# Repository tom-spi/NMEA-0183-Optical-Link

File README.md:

# NMEA-0183-Optical-Link
FdEng Marine Electrical &amp; Electronic: Final Project. NMEA 0183 multiplexed fiber optic link. 
# Abstract
The standardised protocol between navigation & communication equipment on board merchant vessels is NMEA 0183. The NMEA 0183 protocol utilises the TIA/EIA 422-B serial data standard as its transmission medium [1]. The TIA/EIA 422-B standard (Commonly referred to as RS422), is a balanced double-current interchange circuit that supports data rates of up to 10Mbit/s [2]. The electrical configuration of RS422 employs a matched twisted pair that can support wire lengths of up to 4Km. In practice, shielded data cable (CAT5 STP & above) is commonly employed which offers good noise immunity to some extent. The effective noise immunity and long transmission distances can only be achieved given correct termination and separation from EMI & noise sources. 

On board a vessel, there may be a need to run long lengths of NMEA (or any RS422/485 type protocol) through areas of high EMI or electrical noise. For example, a transducer mounted on the aft of the vessel may have to run its NMEA cable(s) via the engine room to reach the bridge, this may pass through switchboard rooms, converter rooms and may also be run alongside or very close to high voltage conductors. All these areas can pose challenges due to the high levels of electrical noise and EMI. 

Utilising an optical based link means the transmission medium for the NMEA data is completely immune to any sources of noise, meaning the optical cable can be run alongside any other conductor. This can reduce costs by eliminating the need for extra deck/bulkhead penetrations, fire rated glands and additional time needed to implement the segregation of power and data conductors. Along with this, the fibre can be used as a “backbone”, carrying multiple NMEA sentences down a single fibre, eliminating the need to run multiple fibres or multiple STP cables. This can be particularly useful in a situation where there is a cluster of NMEA devices located a considerable distance from the bridge (i.e. up forward or up mast). Additionally, there is no possibility of ground loops across the optical link and the NMEA devices at each end of the optical link can be considered to be optically isolated from one another.

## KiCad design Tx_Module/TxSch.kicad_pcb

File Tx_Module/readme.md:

This folder contains the KiCAD files, PCB Gerber files and software written for the Tx Module.

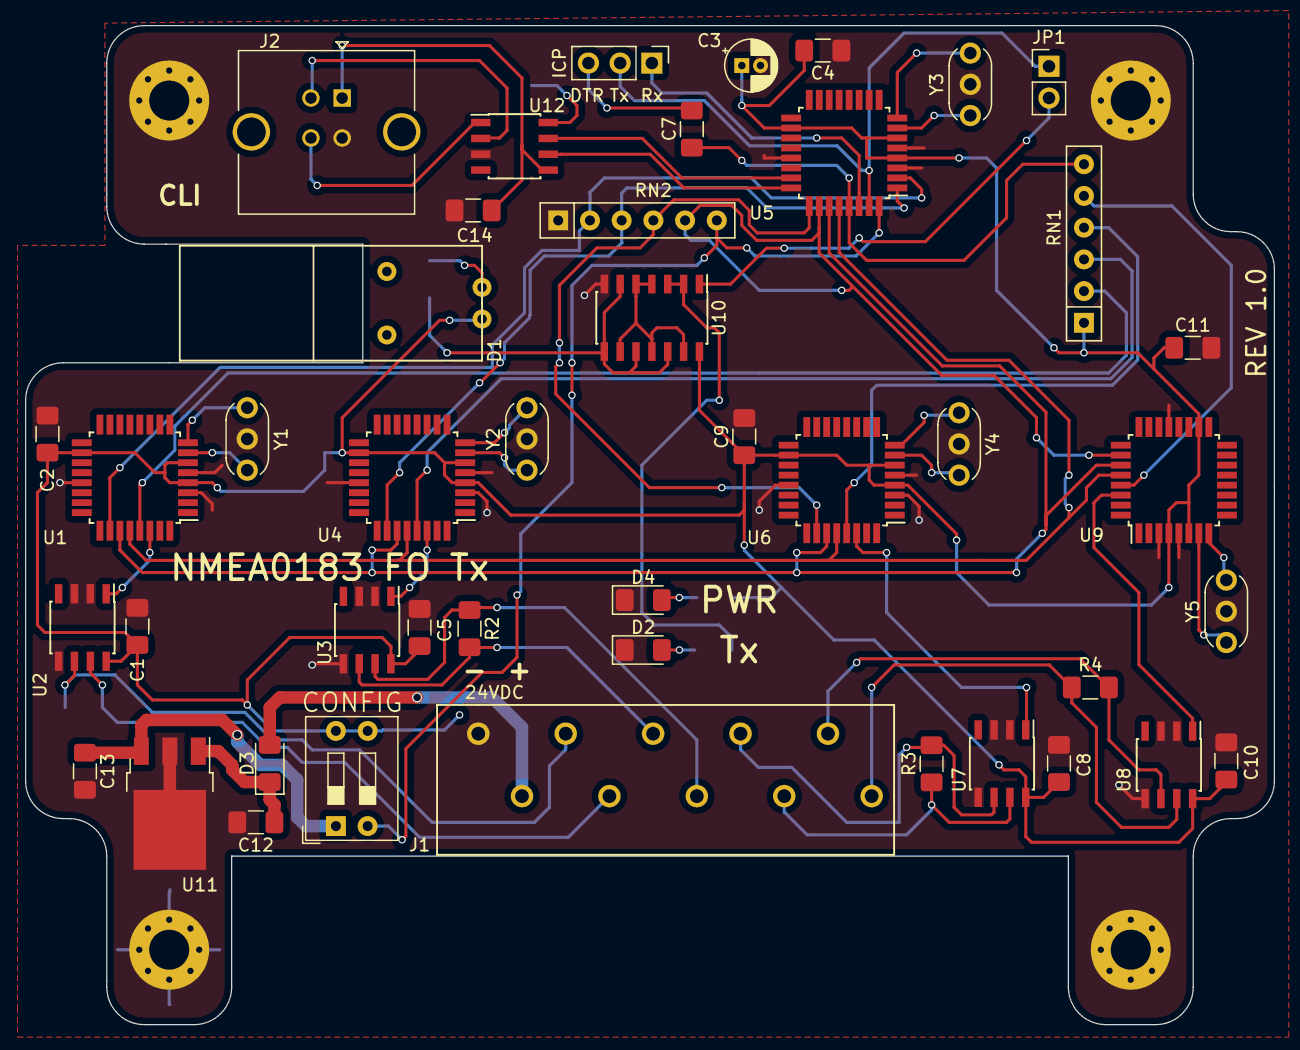
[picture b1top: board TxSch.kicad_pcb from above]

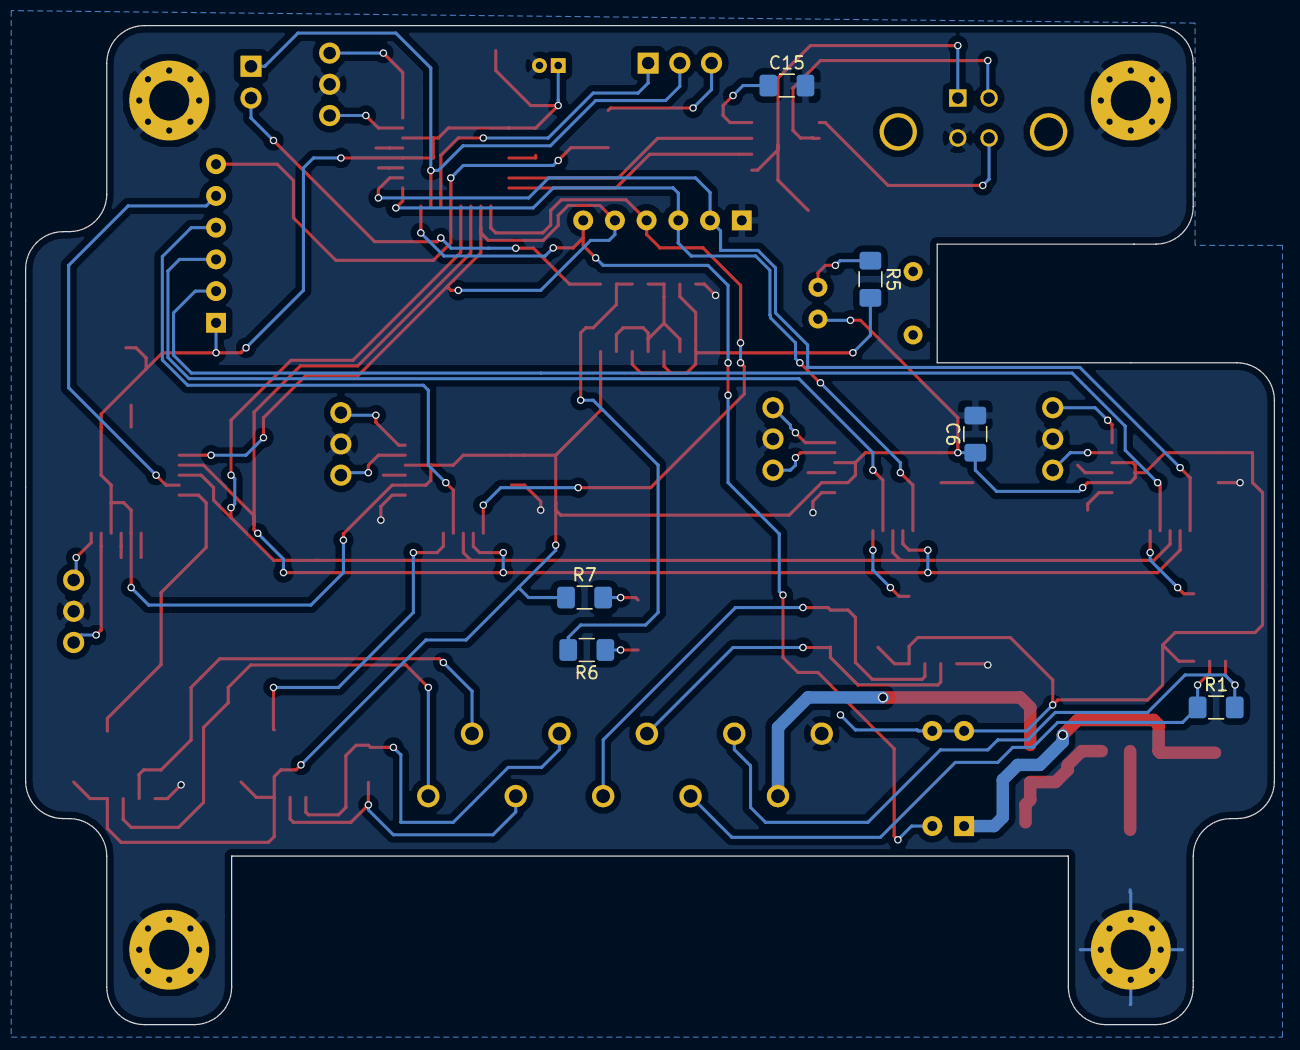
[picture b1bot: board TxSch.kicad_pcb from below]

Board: 2 copper layers, 100.0 x 80.0 mm, 50 parts (6 on the bottom side), 55 nets.

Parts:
C1, C2, C4, C5, C6, C7, C8, C9, C10, C11, C13, C14, C15: 0.1uF; C_1206_3216Metric_Pad1.42x1.75mm_HandSolder
C3: 4.7uF; CP_Radial_D4.0mm_P1.50mm
C12: 0.22uF; C_1206_3216Metric_Pad1.42x1.75mm_HandSolder
CONFIG: SW_DIP_x02; SW_DIP_SPSTx02_Slide_9.78x7.26mm_W7.62mm_P2.54mm
D1: SFH756V
D2: Tx; LED_1206_3216Metric_Pad1.42x1.75mm_HandSolder
D3: 1N4001W; D_1206_3216Metric_Pad1.42x1.75mm_HandSolder
D4: PWR; LED_1206_3216Metric_Pad1.42x1.75mm_HandSolder
ICP: ICP; PinHeader_1x03_P2.54mm_Vertical
J1: PwR & NMEA In; 10PPush_in_Conn
J2: CLI_USB; USB_B_TE_5787834_Vertical
JP1: ICP; PinHeader_1x02_P2.54mm_Vertical
R1, R2, R3, R4: 120R; R_1206_3216Metric_Pad1.42x1.75mm_HandSolder
R5, R6, R7: 330R; R_1206_3216Metric_Pad1.42x1.75mm_HandSolder
RN1, RN2: 10K; R_Array_SIP6
U1, U4, U5, U6, U9: ATmega328P-AU; TQFP-32_7x7mm_P0.8mm
U2, U3, U7, U8: MAX485E; SOIC-8_3.9x4.9mm_P1.27mm
U10: 74HC14; SOIC-14_3.9x8.7mm_P1.27mm
U11: L7805; TO-252-3_TabPin2
U12: CH330N; SOIC-8_3.9x4.9mm_P1.27mm
Y1, Y2, Y3, Y4, Y5: 16MHz; Resonator-3Pin_W6.0mm_H3.0mm

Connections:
+5V: C1.1, C2.1, C3.1, C4.1, C5.1, C6.1, C8.1, C9.1, C10.1, C11.1, CONFIG.3, CONFIG.4, D1.2, R7.1, RN1.1, U1.4, U1.6, U1.18, U2.8, U3.8, U4.4, U4.6, U4.18, U5.4, U5.6, U5.18, U6.4, U6.6, U6.18, U7.8, U8.8, U9.4, U9.6, U9.18, U10.14
/A_RTS: RN2.2, U1.26, U5.2
/B_RTS: RN2.3, U4.26, U5.1
/CLI_EN: CONFIG.2, RN2.6, U5.32
/C_RTS: RN2.4, U5.25, U6.26
/D_RTS: RN2.5, U5.26, U9.26
/FO_Tx: JP1.2, U10.1
/PwR_Sw: C13.1, CONFIG.1, U11.3
/R1: RN1.2, U1.29
/R2: RN1.3, U4.29
/R3: RN1.4, U6.29
/R4: RN1.5, U9.29
/R_MUX: C7.1, RN1.6, U5.29
/RxA_+: J1.3, R1.2, U2.6
/RxA_-: J1.4, R1.1, U2.7
/RxB_+: J1.5, R2.2, U3.6
/RxB_-: J1.6, R2.1, U3.7
/RxC_+: J1.7, R3.2, U7.6
/RxC_-: J1.8, R3.1, U7.7
/RxD_+: J1.9, R4.2, U8.6
/RxD_-: J1.10, R4.1, U8.7
/Rx_A_TTL: U1.30, U2.1
/Rx_B_TTL: U3.1, U4.30
/Rx_C_TTL: U6.30, U7.1
/Rx_D_TTL: U8.1, U9.30
/SCL: U1.28, U4.28, U5.28, U6.28, U9.28
/SDA: U1.27, U4.27, U5.27, U6.27, U9.27
/UART_DTR: C7.2, ICP.3
/UART_Rx: ICP.1, U5.30
/UART_Tx: ICP.2, JP1.1, U5.31
/USB_Rx: U5.23, U12.7
/USB_Tx: U5.24, U12.6
GND: C1.2, C2.2, C3.2, C4.2, C5.2, C6.2, C8.2, C9.2, C10.2, C11.2, C12.2, C13.2, C14.2, C15.2, D2.1, D4.1, J1.1, J2.4, RN2.1, U1.3, U1.5, U1.21, U2.2, U2.3, U2.5, U3.2, U3.3, U3.5, U4.3, U4.5, U4.21, U5.3, U5.5, U5.21, U6.3, U6.5, U6.21, U7.2, U7.3, U7.5, U8.2, U8.3, U8.5, U9.3, U9.5, U9.21, U10.7, U11.2, U12.3, Y1.2, Y2.2, Y3.2, Y4.2, Y5.2
unnamed: C12.1, D3.1, U11.1
unnamed: C14.1, J2.1, U12.5
unnamed: C15.1, U12.8
unnamed: D1.1, R5.1
unnamed: D2.2, R6.1
unnamed: D3.2, J1.2
unnamed: D4.2, R7.2
unnamed: J2.2, U12.2
unnamed: J2.3, U12.1
unnamed: R5.2, U10.6, U10.8, U10.10, U10.12
unnamed: R6.2, U10.2, U10.3
unnamed: U1.7, Y1.3
unnamed: U1.8, Y1.1
unnamed: U4.7, Y2.1
unnamed: U4.8, Y2.3
unnamed: U5.7, Y3.1
unnamed: U5.8, Y3.3
unnamed: U6.7, Y4.3
unnamed: U6.8, Y4.1
unnamed: U9.7, Y5.1
unnamed: U9.8, Y5.3
unnamed: U10.4, U10.5, U10.9, U10.11, U10.13

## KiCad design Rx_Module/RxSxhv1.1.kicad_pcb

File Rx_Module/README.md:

This folder contains the KiCAD files, PCB Gerber files and software written for the Rx Module.

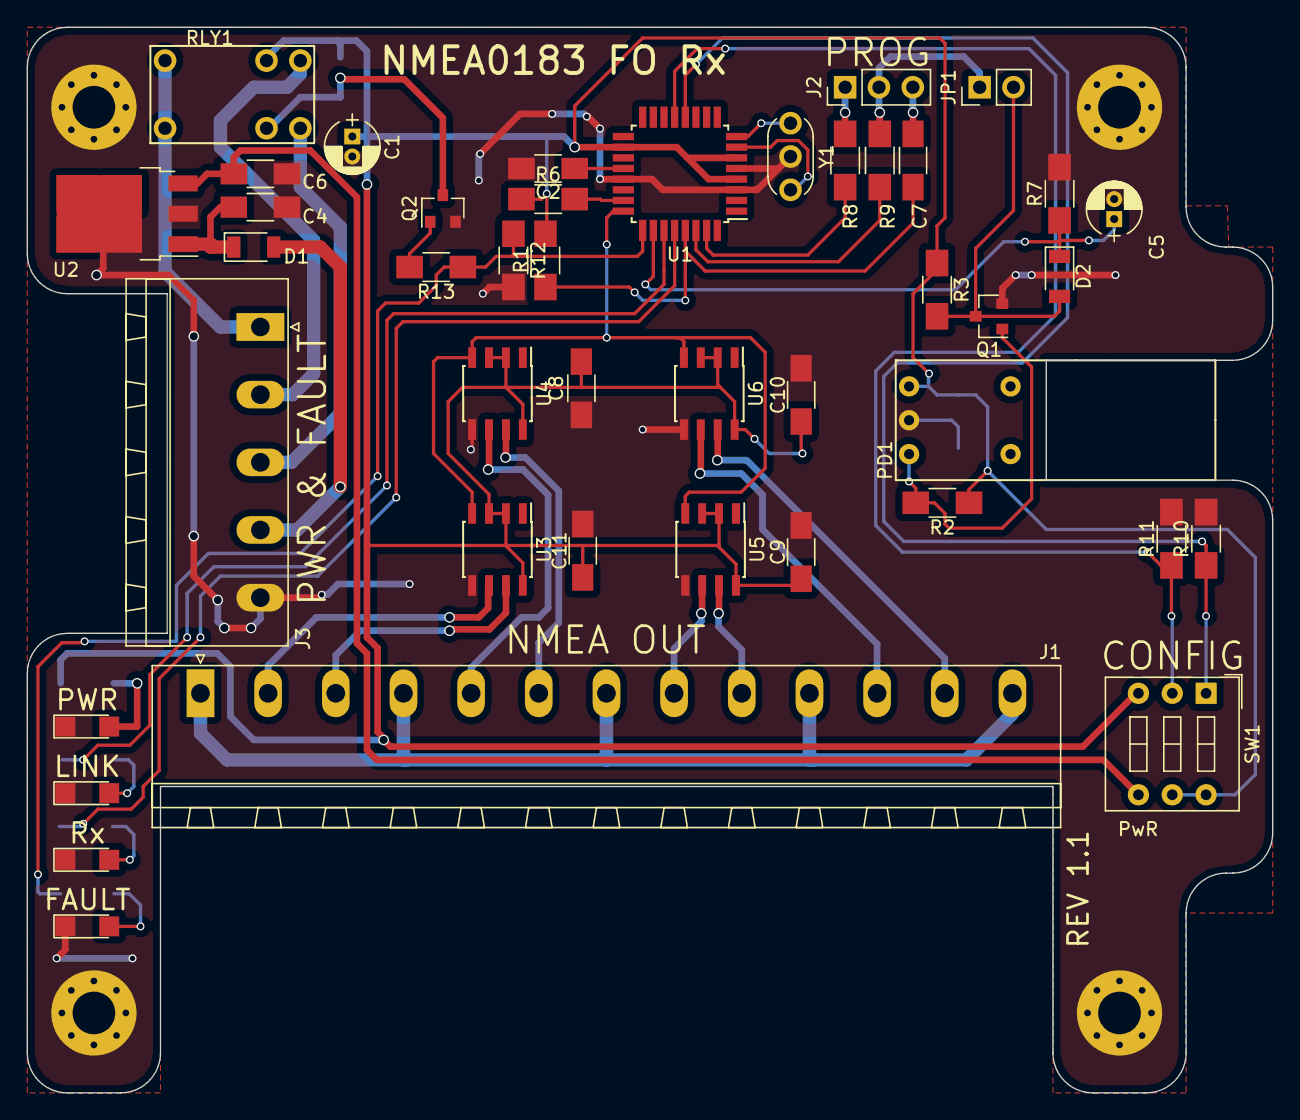
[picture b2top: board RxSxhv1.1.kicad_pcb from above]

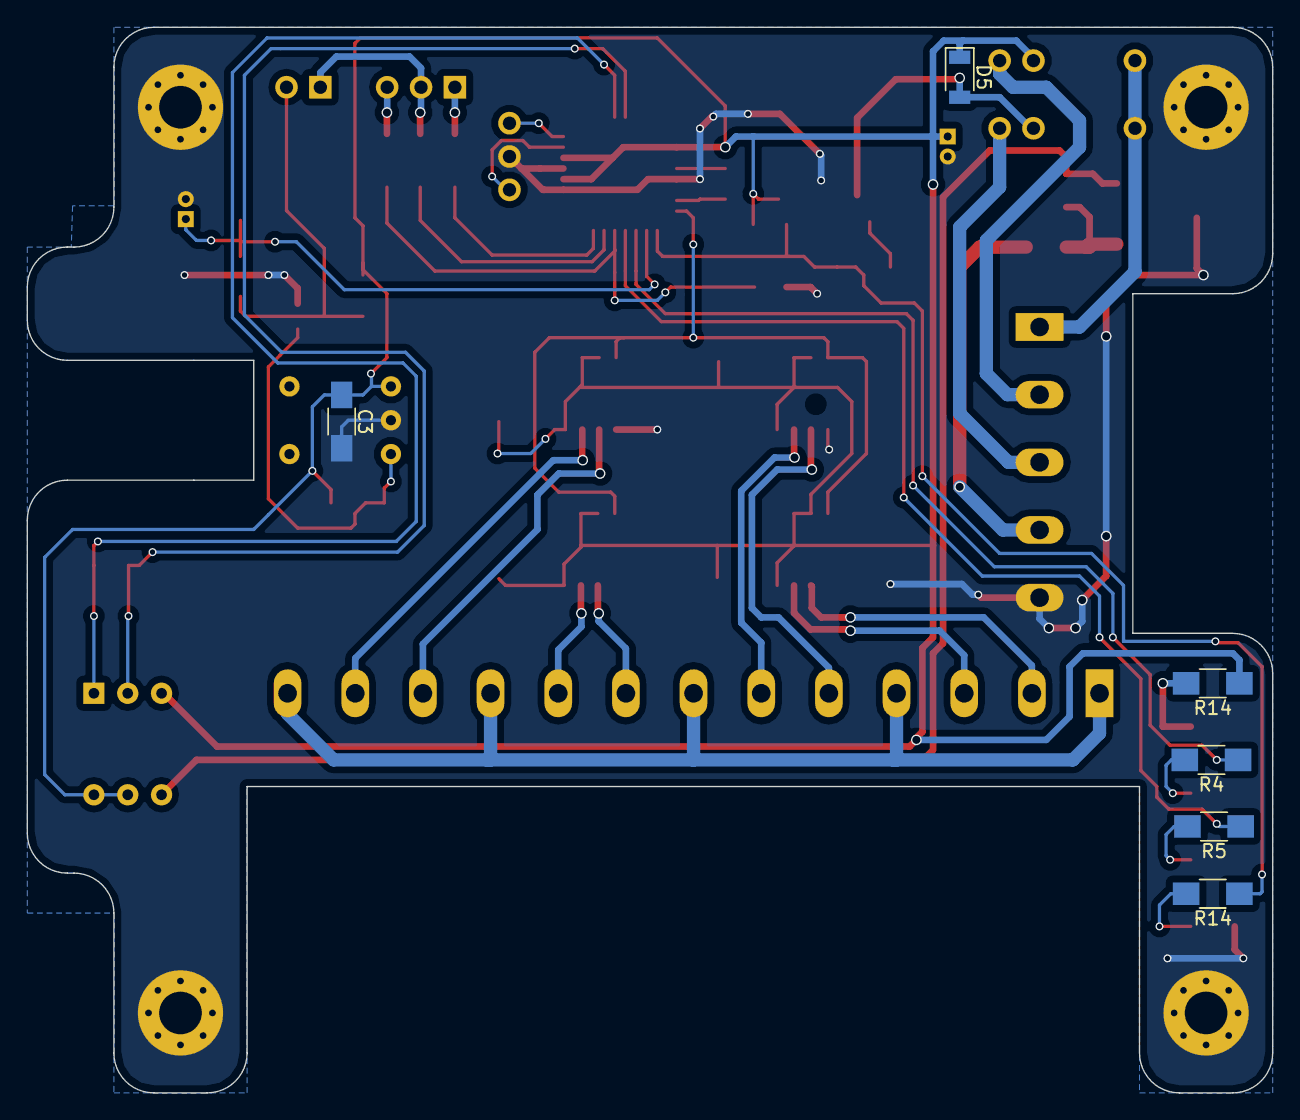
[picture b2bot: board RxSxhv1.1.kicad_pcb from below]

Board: 2 copper layers, 93.5 x 80.0 mm, 49 parts (6 on the bottom side), 41 nets.

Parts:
C1: 4.7u; CP_Radial_D4.0mm_P1.50mm
C2, C7: 100n; C_1206_HandSoldering
C3: 100nF; C_1206_HandSoldering
C4: 0.22u; C_1206_HandSoldering
C5: 4.7uF; CP_Radial_D4.0mm_P1.50mm
C6, C8, C9, C10, C11: 0.1u; C_1206_HandSoldering
D1, D2, D5: 1N4001W; D_1206
FAULT: LED_1206
J1: NMEA; PhoenixContact_MSTBA-G_13x5.08mm_Angled
J2: Prog; Pin_Header_Straight_1x03_Pitch2.54mm
J3: PwR & Fault; PhoenixContact_MSTBA-G_05x5.08mm_Angled
JP1: Jumper_NC_Small; Pin_Header_Straight_1x02_Pitch2.54mm
LINK: Link; LED_1206
PD1: SFH551
PWR: PwR; LED_1206
Q1, Q2: 2N3904; SOT-23
R1, R2, R3, R6, R10, R11: 10K; R_1206_HandSoldering
R4, R5, R14, R14#2: 330R; R_1206_HandSoldering
R7: 100K; R_1206_HandSoldering
R8, R9: 1K; R_1206_HandSoldering
R12: 10k; R_1206_HandSoldering
R13: 1k; R_1206_HandSoldering
RLY1: G5V-1
Rx: Rx; LED_1206
SW1: Config; SW_DIP_x3_W7.62mm_Slide
U1: ATMEGA328P-AU; TQFP-32_7x7mm_Pitch0.8mm
U2: L7805; TO-252-3_TabPin4
U3, U4, U5, U6: MAX485E; SOIC-8_3.9x4.9mm_Pitch1.27mm
Y1: 16MHz; Resonator-3pin_w6.0mm_h3.0mm

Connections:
+5V: C1.1, C3.1, C8.1, C9.1, C10.1, C11.1, D5.1, PD1.3, R1.2, R2.1, R3.1, R6.1, R14#2.1, RLY1.4, SW1.3, SW1.5, SW1.6, U1.4, U1.6, U1.18, U3.2, U3.3, U3.8, U4.2, U4.3, U4.8, U5.2, U5.3, U5.8, U6.2, U6.3, U6.8
/+5V_Sw: C6.1, SW1.4, U2.3
/COM: J3.1, RLY1.5, RLY1.6
/Config_0: R10.1, SW1.1, U1.12
/Config_1: R11.1, SW1.2, U1.13
/Fibre_Rx_TTL: D2.2, JP1.2, Q1.3, R3.2
/Link: C5.1, D2.1, R7.1, U1.26
/Link_Fail: R12.1, R13.1, R14.1, U1.25
/Link_Fail_NC: J3.3, RLY1.2
/Link_Fail_NO: J3.2, RLY1.1
/Link_LED: R4.1, U1.27
/PwR: D1.2, J3.4
/RS422TTL: U1.24, U3.4, U4.4, U5.4, U6.4
/RX_LED: R5.1, U1.28
/Reset: C7.1, R1.1, U1.29
/TxA+: J1.2, U3.6
/TxA-: J1.3, U3.7
/TxB+: J1.5, U4.6
/TxB-: J1.6, U4.7
/TxC+: J1.8, U5.6
/TxC-: J1.9, U5.7
/TxD+: J1.11, U6.6
/TxD-: J1.12, U6.7
Earth: J1.1, J1.4, J1.7, J1.10, J1.13
GND: C1.2, C2.2, C3.2, C4.2, C5.2, C6.2, C8.2, C9.2, C10.2, C11.2, FAULT.1, J3.5, LINK.1, PD1.2, PWR.1, Q1.2, Q2.2, R7.2, R10.2, R11.2, R12.2, Rx.1, U1.3, U1.5, U1.21, U2.2, U2.4, U3.5, U4.5, U5.5, U6.5, Y1.2
unnamed: C2.1, U1.20
unnamed: C4.1, D1.1, U2.1
unnamed: C7.2, J2.3
unnamed: LINK.2, R4.2
unnamed: R5.2, Rx.2
unnamed: D5.2, Q2.3, RLY1.3
unnamed: PWR.2, R14#2.2
unnamed: J2.1, R9.1
unnamed: J2.2, JP1.1, R8.2
unnamed: PD1.1, Q1.1, R2.2
unnamed: Q2.1, R13.2
unnamed: R6.2, U1.23
unnamed: R8.1, U1.30
unnamed: R9.2, U1.31
unnamed: U1.7, Y1.3
unnamed: U1.8, Y1.1

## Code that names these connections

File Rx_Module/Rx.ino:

/*
|--------------------------------------------------------------------------------------------|
|                        --NMEA 0183 OPTICAL LINK Rx MODULE--                                |
|                                                                                            |
|                                                                                            |
|  Project        NMEA_FO.proj                                                               |
|  Program Name 	Rx_v1.1.ino                                                                |
|  Author		     	Thomas Spires 															                               |
|															                                                               |
|  Author Info:                                                                              |
|  Firmware to be written to U1 (ATMEGA328P) on Rx PCB: refer to KiCAD .kicad_pcb            |
|  "RxPCBV1.1"                                                                               |
|                                                                                            |
|  Revision Release Info:                                                                    |
|  20181210 00:42    Tspires      1.0      Initial Deployment on prototype PCB               |
|  20181219 03:13    Tspires      1.1      Added baud rate config + link status              |
|										   function.                                                             |
|--------------------------------------------------------------------------------------------|
*/

#include <SoftwareSerial.h>					//include Bit-Banged serial port hex files

SoftwareSerial RS422Serial(A0, A1); 		// RX, TX // Set BitBanged serial port registers accordingly

// Declare Global Variables

char rx_byte;								//Initialise ASCII Char byte to be passed from Hardware UART buffer

// Declare Pin Names

#define RX_LED A5
#define Link_LED A4
#define Link_Stat A3
#define Link_Fail A2
#define Config_Bit0 8
#define Config_Bit1 9

//Initialise Registers & Interfaces

void setup() {
  //Initialise UARTs
  Serial.begin(19200);						//Start hardware UART & set registers for 19200 Baud
  //Set GPIO Registers
  pinMode(Config_Bit0, INPUT);
  pinMode(Config_Bit1, INPUT);
  pinMode(Link_Stat, INPUT);
  pinMode(RX_LED, OUTPUT);
  pinMode(Link_LED, OUTPUT);
  pinMode(Link_Fail, OUTPUT);
  
  // Set output baud rate dependant on Config DIP switch settings
  
  if (digitalRead(Config_Bit0) == 0 && digitalRead(Config_Bit1) == 0){	//Switches 0 0 
    RS422Serial.begin(2400);											//Set NMEA Baud to 2400                      
  }	
  if (digitalRead(Config_Bit0) == 1 && digitalRead(Config_Bit1) == 0){  //Switches 1 0 
    RS422Serial.begin(4800);											//Set NMEA Baud to 4800
  }
  if (digitalRead(Config_Bit0) == 0 && digitalRead(Config_Bit1) == 1){	//Switches 0 1 
    RS422Serial.begin(9600);											//Set NMEA Baud to 9600
  }
  if (digitalRead(Config_Bit0) == 1 && digitalRead(Config_Bit1) == 1){	//Switches 1 1 		
    RS422Serial.begin(19200);											//Set NMEA Baud to 19200;
  }
}

void loop() {						   //Function will loop continuoisly to check link status and contents of fibre UART input buffer
  if (digitalRead(Link_Stat) == 0 ) {  //Link Status 'LOW' detected - link down
    digitalWrite(Link_LED, LOW);	   //Disable LED Link 'ok' indication
    digitalWrite(Link_Fail, HIGH);	   //Set Link fault output 'HIGH' - LED + Relay
  }
  else {							   //Link status other than 'LOW' detected
    digitalWrite(Link_LED, HIGH);	   //Enable LED Link 'ok' indication
    digitalWrite(Link_Fail, LOW);	   //Set Link fault output 'LOW' - LED + Relay
  }
  while (Serial.available() > 0) {	   //Will check contents of fibre UART input buffer, if any data is in the buffer -> enter loop
    digitalWrite(RX_LED, HIGH);		   //Set Rx LED inidcation 'HIGH'
    rx_byte = Serial.read();		   //Read contents of Fibre UART input buffer at 19200 baud and place contents into rx_byte
    RS422Serial.print(rx_byte);		   //Re-transmit rx_byte out the software UART to the max485s at the configured baud rate 
    }
   digitalWrite(RX_LED, LOW);		   //If not in the reciving loop, set Rx LED indication 'LOW'
   }
